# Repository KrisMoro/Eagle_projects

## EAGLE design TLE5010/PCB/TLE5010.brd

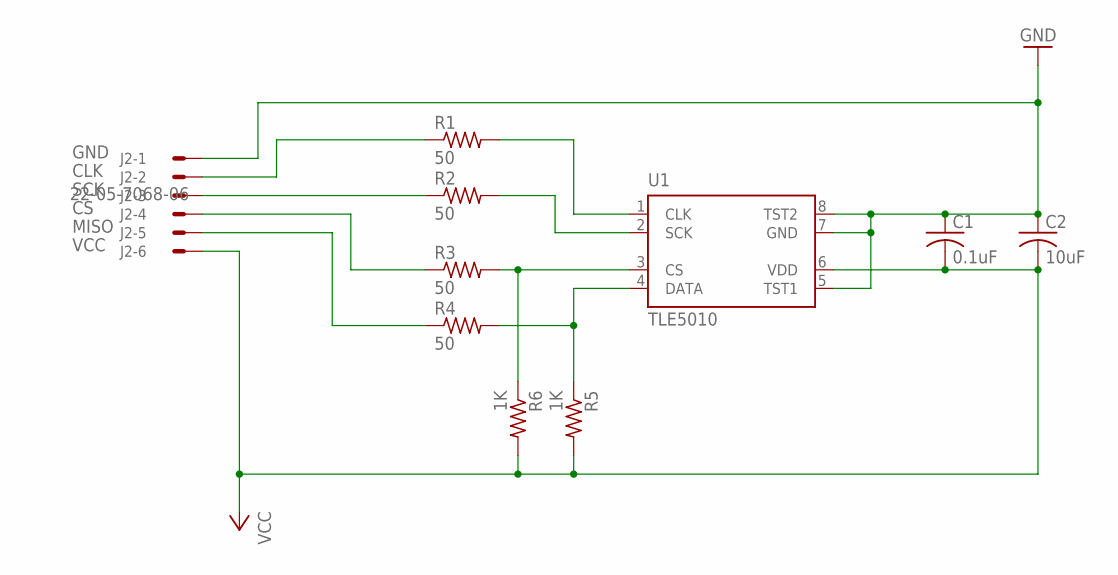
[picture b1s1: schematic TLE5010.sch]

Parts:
C1: 0.1uF; C1206
C2: 10uF; C1206
J2: 22-05-7068-06; 7395-06
R1, R2, R3, R4: 50; R1206
R5, R6: 1K; R1206
U1: TLE5010; PG-DSO-8

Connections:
CLK: J2.2, R1.1
CS: J2.4, R3.1
DATA: R4.2, R5.1, U1.4 (DATA)
GND: C1.1, C2.1, J2.1, U1.5 (TST1), U1.7 (GND), U1.8 (TST2)
MISO: J2.5, R4.1
unnamed: R1.2, U1.1 (CLK)
unnamed: R2.2, U1.2 (SCK)
unnamed: R3.2, R6.1, U1.3 (CS)
SCK: J2.3, R2.1
VCC: C1.2, C2.2, J2.6, R5.2, R6.2, U1.6 (VDD)

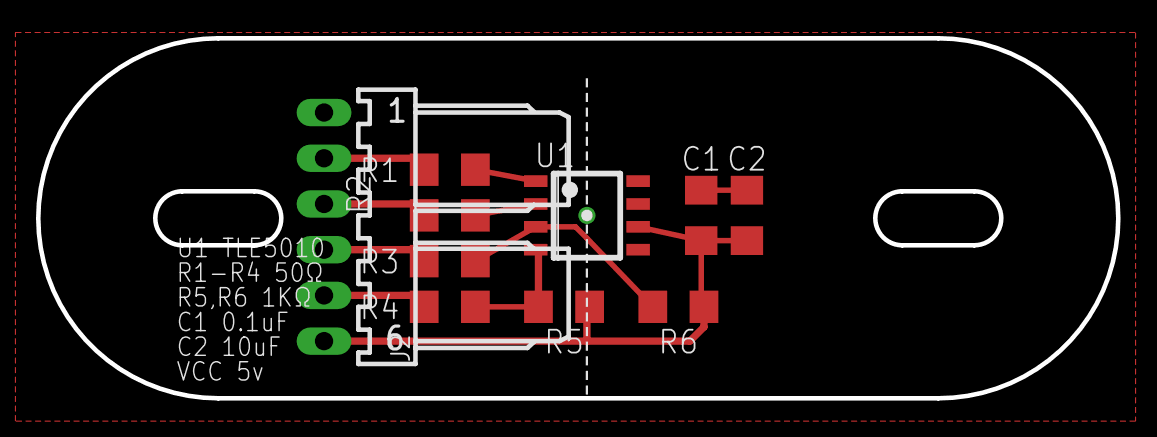
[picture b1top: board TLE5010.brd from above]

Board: 2 copper layers, 60.0 x 20.0 mm, 10 parts (0 on the bottom side), 10 nets.

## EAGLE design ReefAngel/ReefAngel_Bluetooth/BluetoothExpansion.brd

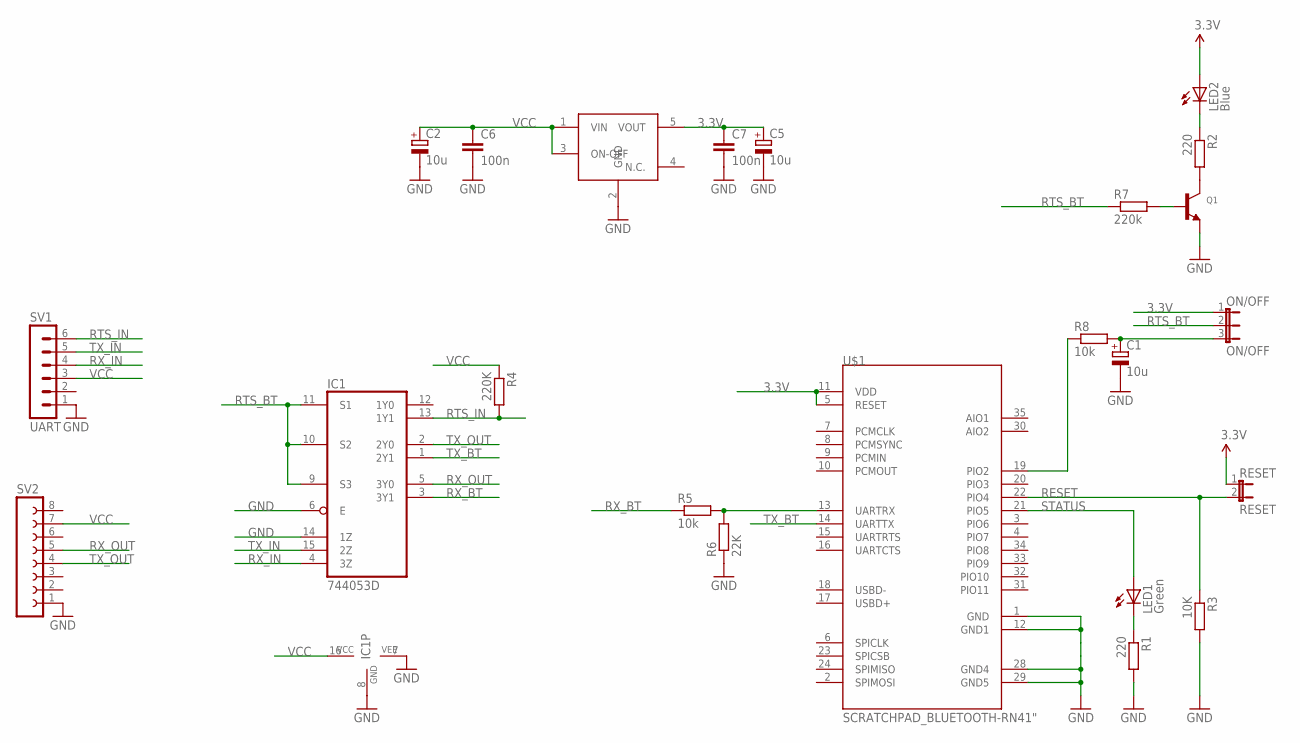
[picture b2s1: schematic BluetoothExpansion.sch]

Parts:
C1, C2, C5: 10u; A/3216-18W
C6, C7: 100n; C0805
IC1: 744053D; SO16
LED1: Green; LED3MM
LED2: Blue; LED3MM
ON/OFF: ON/OFF; JP2
Q1: TRANSISTOR_NPN; SOT23-R
R1, R2: 220; R0805
R3: 10K; R0805
R4: 220K; R0805
R5, R8: 10k; R0805
R6: 22K; R0805
R7: 220k; R0805
RESET: RESET; JP1
SV1: UART; MA06-1
SV2: FE08-1; FE08
U2: LP2985; SOT23-5
U$1: SCRATCHPAD_BLUETOOTH-RN41"; SCRATCHPAD_RN41

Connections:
3.3V: C5.+, C7.1, ON/OFF.1, U2.5 (VOUT), U$1.5 (RESET), U$1.11 (VDD)
GND: C1.-, C2.-, C5.-, C6.2, C7.2, IC1.6 (E), IC1.7 (VEE), IC1.8 (GND), IC1.14 (1Z), Q1.2 (E), R1.2, R3.2, R6.1, SV1.1, SV2.1, U2.2 (GND), U$1.1 (GND), U$1.12 (GND1), U$1.28 (GND4), U$1.29 (GND5)
unnamed: R5.2, R6.2, U$1.13 (UARTRX)
unnamed: R8.1, U$1.19 (PIO2)
unnamed: LED1.K (C), R1.1
unnamed: LED2.K (C), R2.1
unnamed: Q1.3 (C), R2.2
unnamed: C1.+, ON/OFF.3, R8.2
unnamed: Q1.1 (B), R7.2
RESET: R3.1, RESET.2, U$1.22 (PIO4)
RTS_BT: IC1.9 (S3), IC1.10 (S2), IC1.11 (S1), ON/OFF.2, R7.1
RTS_IN: IC1.13 (1Y1), R4.2, SV1.6
RX_BT: IC1.3 (3Y1), R5.1
RX_IN: IC1.4 (3Z), SV1.4
RX_OUT: IC1.5 (3Y0), SV2.5
STATUS: LED1.A, U$1.21 (PIO5)
TX_BT: IC1.1 (2Y1), U$1.14 (UARTTX)
TX_IN: IC1.15 (2Z), SV1.5
TX_OUT: IC1.2 (2Y0), SV2.4
VCC: C2.+, C6.1, IC1.16 (VCC), LED2.A, R4.1, RESET.1, SV1.3, SV2.7, U2.1 (VIN), U2.3 (ON-OFF)

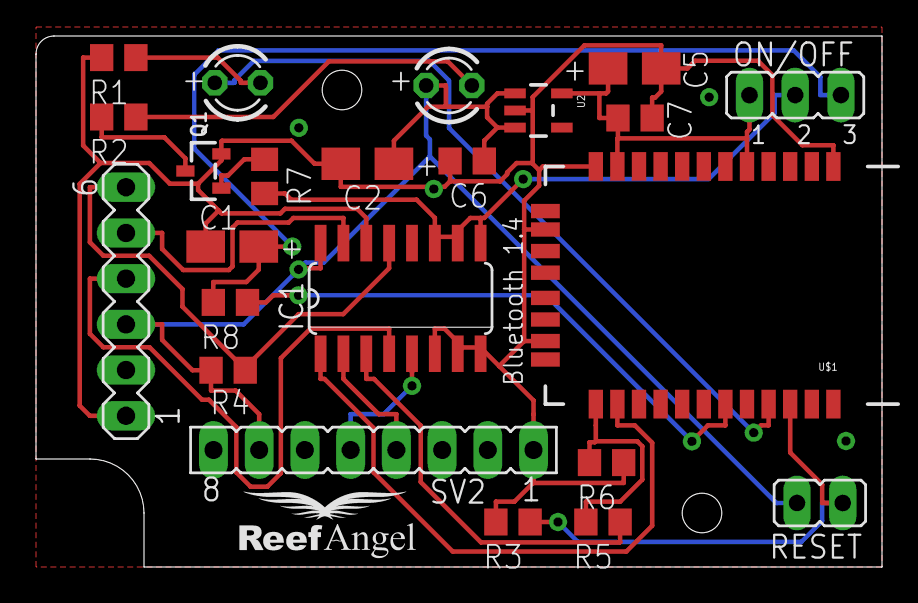
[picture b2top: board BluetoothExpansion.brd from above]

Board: 2 copper layers, 47.0 x 29.5 mm, 23 parts (0 on the bottom side), 20 nets.

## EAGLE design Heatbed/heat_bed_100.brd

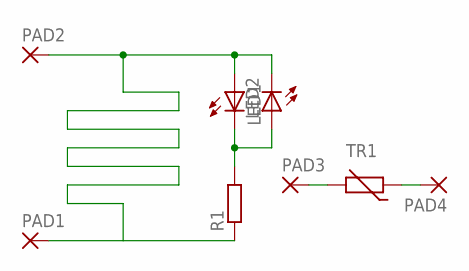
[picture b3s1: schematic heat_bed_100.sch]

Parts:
LED1, LED2: LEDSML0805; SML0805
PAD1, PAD2, PAD3, PAD4: 2,54/1,0
R1: R-EU_M1206; M1206
TR1: THERMISTOR_R-5; R-5

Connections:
unnamed: LED1.A, LED2.C, PAD1.1, PAD2.1, R1.1
unnamed: PAD3.1, TR1.2
unnamed: PAD4.1, TR1.1
unnamed: LED1.C, LED2.A, R1.2

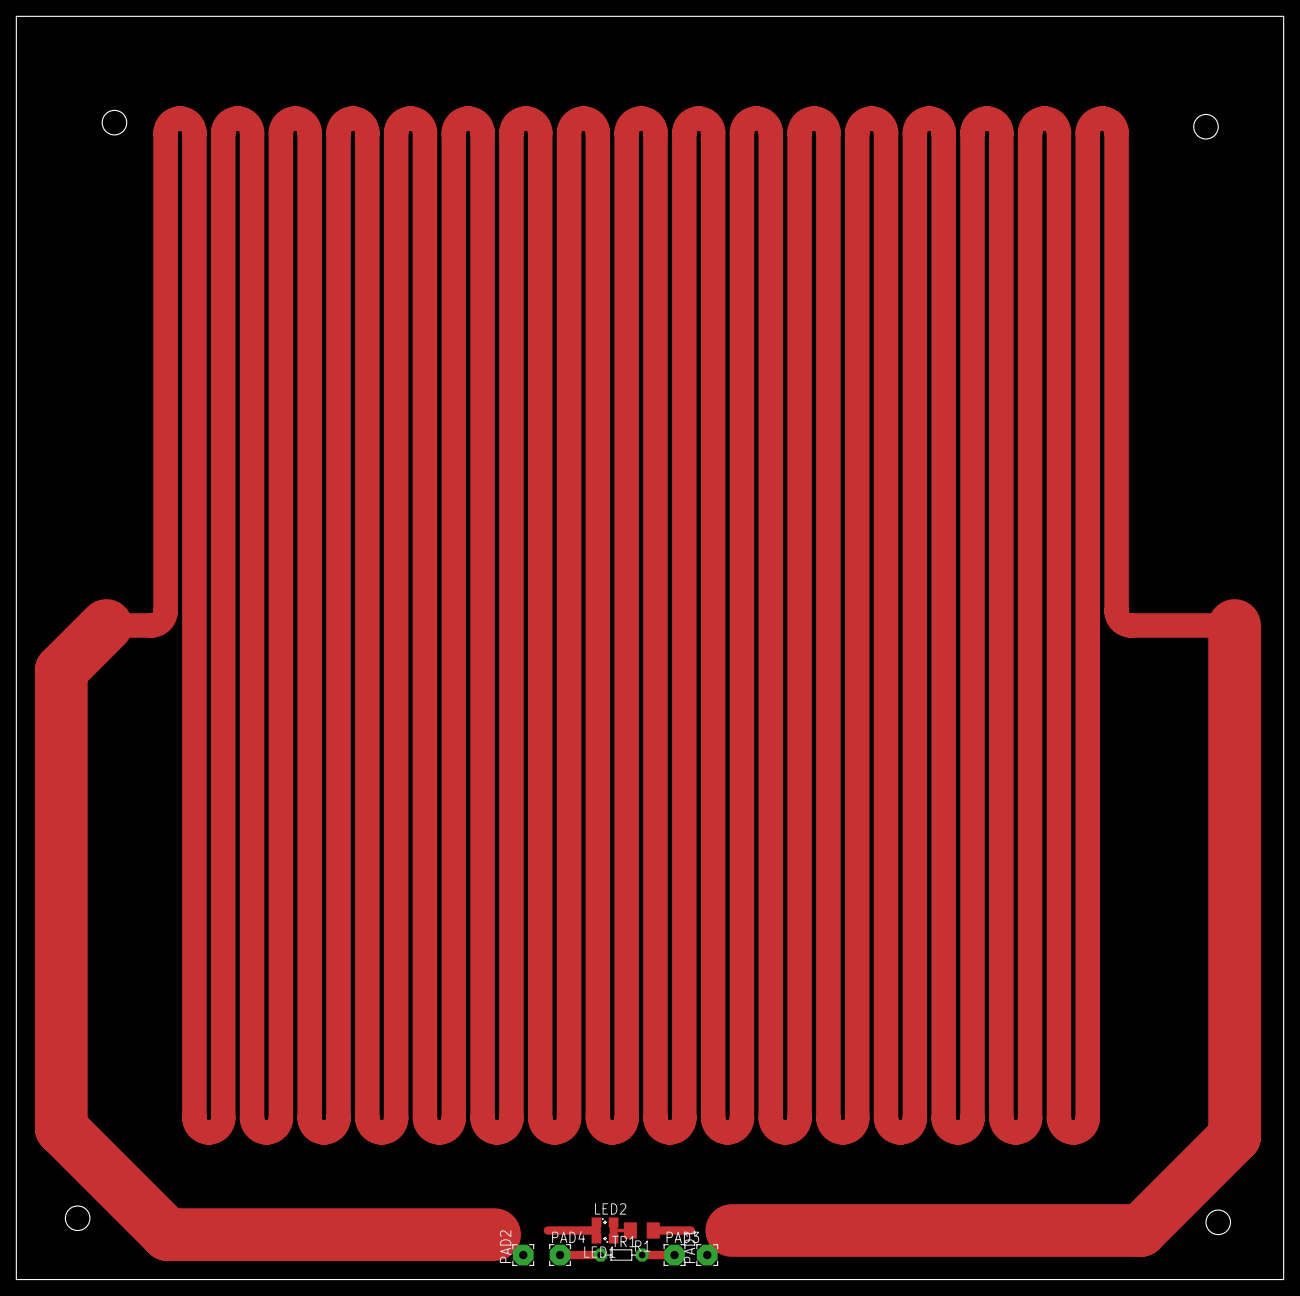
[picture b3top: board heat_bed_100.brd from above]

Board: 2 copper layers, 155.0 x 154.5 mm, 8 parts (0 on the bottom side), 4 nets.

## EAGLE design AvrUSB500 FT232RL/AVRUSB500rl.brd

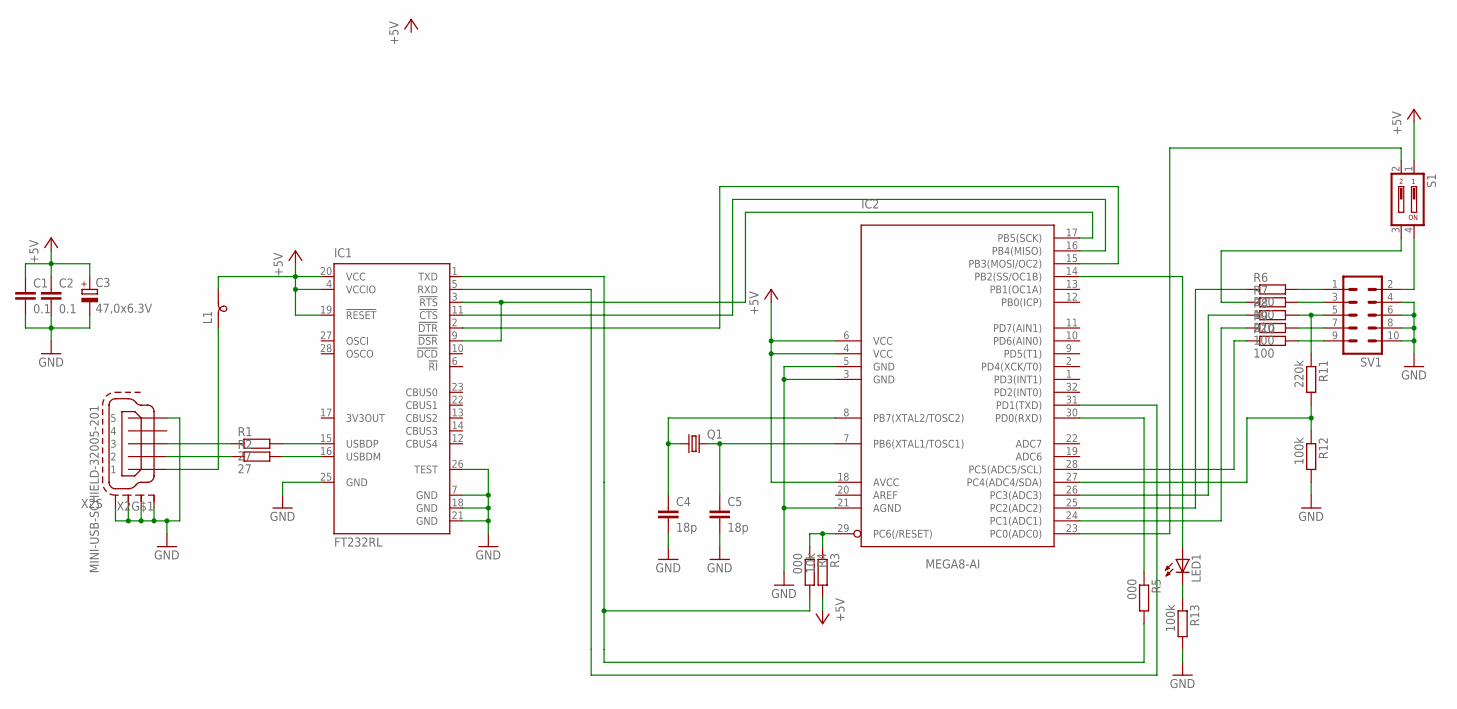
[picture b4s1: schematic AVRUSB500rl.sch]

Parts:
C1, C2: 0.1; C0805
C3: 47,0x6.3V; 153CLV-0605
C4, C5: 18p; C0805
IC1: FT232RL; SSOP28
IC2: MEGA8-AI; TQFP32-08
L1: SM-B5
LED1: LED3MM
Q1: CRYSTALHC49UP; HC49UP
R1, R2: 27; R0805
R3: 10k; R0805
R4, R5: 000; R0805
R6, R8: 220; R0805
R7, R9, R10: 100; R0805
R11: 220k; R0805
R12, R13: 100k; R0805
S1: DA02; DA-02
SV1: ML10L
X2: MINI-USB-SCHIELD-32005-201; 32005-201

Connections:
+5V: C1.1, C2.1, C3.+, IC2.4 (VCC), IC2.6 (VCC), IC2.18 (AVCC), R3.2, S1.1
GND: C1.2, C2.2, C3.-, C4.2, C5.2, IC1.7 (GND), IC1.18 (GND), IC1.21 (GND), IC1.25 (GND), IC1.26 (TEST), IC2.3 (GND), IC2.5 (GND), IC2.21 (AGND), R12.2, R13.2, SV1.4, SV1.6, SV1.8, SV1.10, X2.5, X2.M1 (S1), X2.M2 (S2), X2.M3 (S3), X2.M4 (S4)
unnamed: R1.1, X2.3
unnamed: IC1.15 (USBDP), R1.2
unnamed: R2.1, X2.2
unnamed: IC1.16 (USBDM), R2.2
unnamed: R6.2, SV1.1
unnamed: C4.1, IC2.8 (PB7(XTAL2/TOSC2)), Q1.1
unnamed: C5.1, IC2.7 (PB6(XTAL1/TOSC1)), Q1.2
unnamed: IC2.29 (PC6(/RESET)), R3.1, R4.1
unnamed: IC1.1 (TXD), R4.2, R5.2
unnamed: IC2.30 (PD0(RXD)), R5.1
unnamed: R7.2, SV1.3
unnamed: IC1.5 (RXD), IC2.31 (PD1(TXD))
unnamed: IC1.3 (!RTS), IC1.9 (!DSR), IC2.17 (PB5(SCK))
unnamed: IC1.11 (!CTS), IC2.16 (PB4(MISO))
unnamed: IC1.2 (!DTR), IC2.15 (PB3(MOSI/OC2))
unnamed: R8.2, R11.1, SV1.5
unnamed: R9.2, SV1.7
unnamed: R10.2, SV1.9
unnamed: IC2.27 (PC4(ADC4/SDA)), R11.2, R12.1
unnamed: IC2.28 (PC5(ADC5/SCL)), R10.1
unnamed: R7.1, S1.3
unnamed: L1.1, X2.1
unnamed: IC2.24 (PC1(ADC1)), R9.1
unnamed: IC2.26 (PC3(ADC3)), R8.1
unnamed: IC2.25 (PC2(ADC2)), R6.1
unnamed: S1.4, SV1.2
unnamed: IC2.23 (PC0(ADC0)), S1.2
unnamed: IC2.14 (PB2(SS/OC1B)), LED1.A
unnamed: LED1.K (C), R13.1
VCC: IC1.4 (VCCIO), IC1.19 (!RESET), IC1.20 (VCC), L1.2

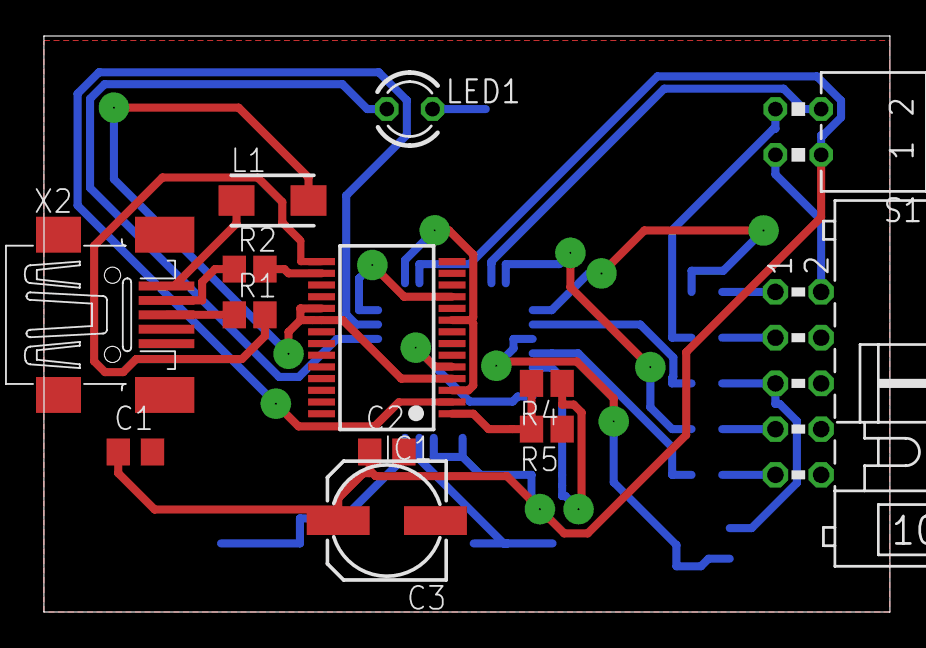
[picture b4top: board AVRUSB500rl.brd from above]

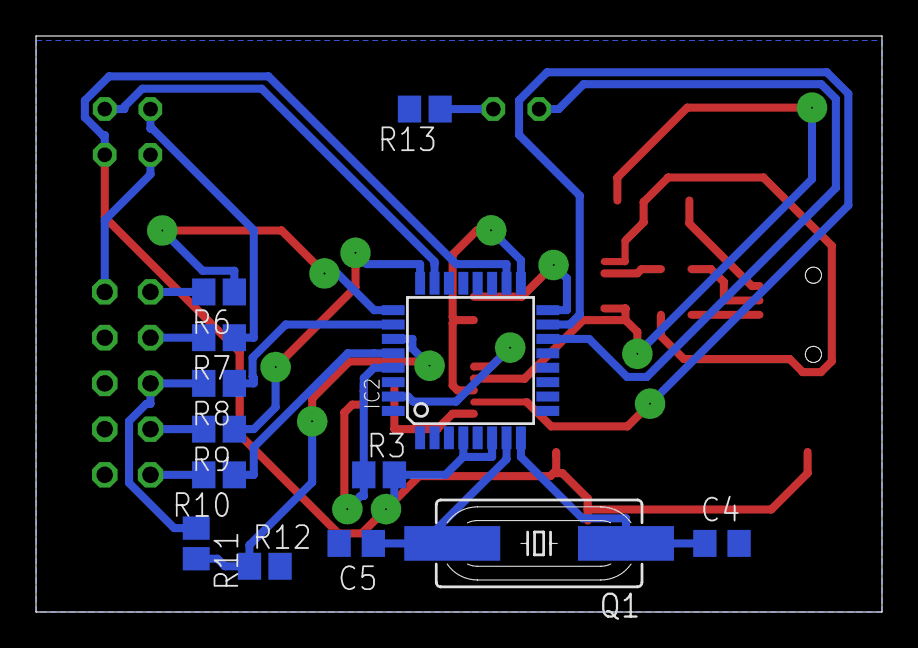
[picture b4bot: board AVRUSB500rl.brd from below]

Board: 2 copper layers, 47.0 x 32.0 mm, 26 parts (13 on the bottom side), 32 nets.

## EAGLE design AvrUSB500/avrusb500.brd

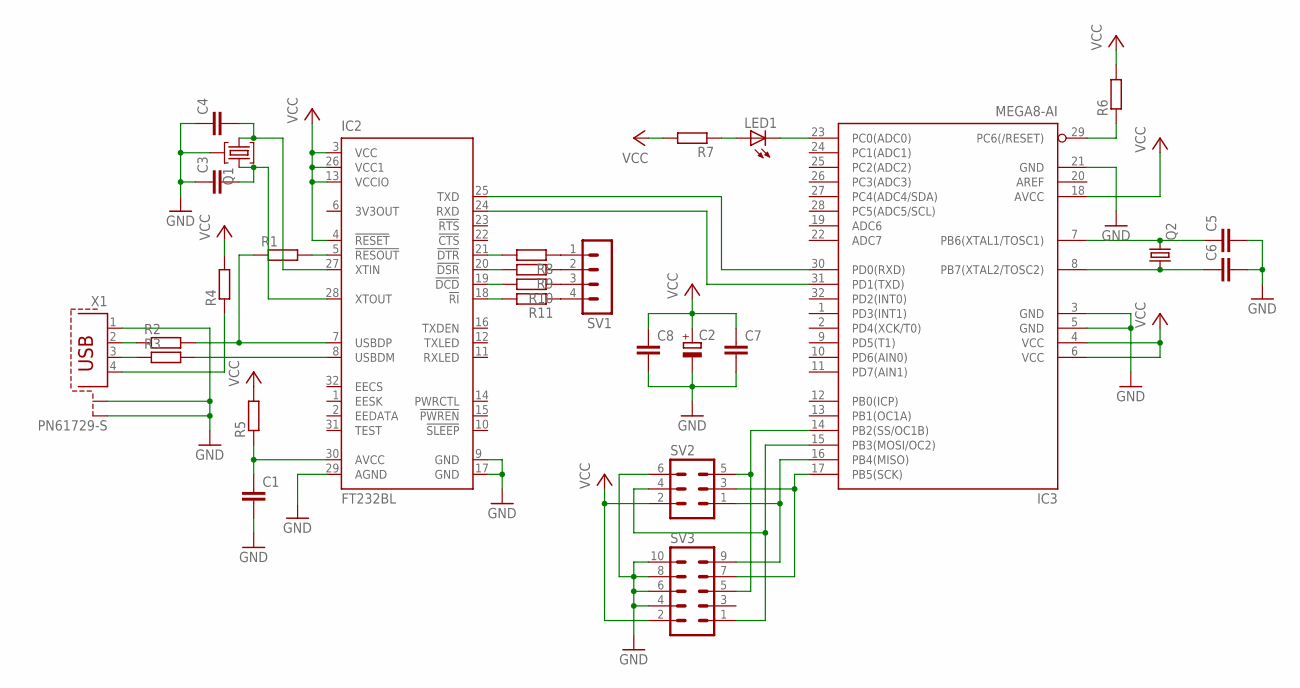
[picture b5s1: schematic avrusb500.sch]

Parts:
C1, C3, C4, C5, C6, C7, C8: C-EUC0805; C0805
C2: CPOL-EUSMCB; SMC_B
IC2: FT232BL; LQFP32-7X7
IC3: MEGA8-AI; TQFP32-08
LED1: LED5MM
Q1: HC49TL-H
Q2: CRYSTALHC49UP; HC49UP
R1, R2, R3, R4, R5, R6, R7, R8, R9, R10, R11: R-EU_R0805; R0805
SV1: MA04-1
SV2: ML6L
SV3: ML10L
X1: PN61729-S

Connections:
GND: C1.2, C2.-, C3.1, C4.1, C5.2, C6.2, C7.2, C8.2, IC2.9 (GND), IC2.17 (GND), IC2.29 (AGND), IC3.3 (GND), IC3.5 (GND), IC3.21 (GND), Q1.3, SV2.6, SV3.4, SV3.6, SV3.8, SV3.10, X1.1, X1.S1, X1.S2
unnamed: IC2.5 (!RESOUT), R1.2
unnamed: IC2.7 (USBDP), R1.1, R2.2
unnamed: IC2.8 (USBDM), R3.2
unnamed: R2.1, X1.2
unnamed: R3.1, X1.3
unnamed: R4.1, X1.4
unnamed: C1.1, IC2.30 (AVCC), R5.1
unnamed: C4.2, IC2.27 (XTIN), Q1.1
unnamed: C3.2, IC2.28 (XTOUT), Q1.2
unnamed: IC2.21 (!DTR), R8.2
unnamed: IC2.25 (TXD), IC3.30 (PD0(RXD))
unnamed: IC2.24 (RXD), IC3.31 (PD1(TXD))
unnamed: C5.1, IC3.7 (PB6(XTAL1/TOSC1)), Q2.2
unnamed: C6.1, IC3.8 (PB7(XTAL2/TOSC2)), Q2.1
unnamed: IC3.29 (PC6(/RESET)), R6.1
unnamed: IC3.15 (PB3(MOSI/OC2)), SV2.4, SV3.1
unnamed: IC3.16 (PB4(MISO)), SV2.1, SV3.9
unnamed: IC3.17 (PB5(SCK)), SV2.3, SV3.7
unnamed: IC3.14 (PB2(SS/OC1B)), SV2.5, SV3.5
unnamed: IC2.20 (!DSR), R9.2
unnamed: IC2.19 (!DCD), R10.2
unnamed: IC2.18 (!RI), R11.2
unnamed: R8.1, SV1.1
unnamed: LED1.A, R7.1
unnamed: IC3.23 (PC0(ADC0)), LED1.K (C)
unnamed: R9.1, SV1.2
unnamed: R10.1, SV1.3
unnamed: R11.1, SV1.4
VCC: C2.+, C7.1, C8.1, IC2.3 (VCC), IC2.4 (!RESET), IC2.13 (VCCIO), IC2.26 (VCC1), IC3.4 (VCC), IC3.6 (VCC), IC3.18 (AVCC), R4.2, R5.2, R6.2, R7.2, SV2.2, SV3.2

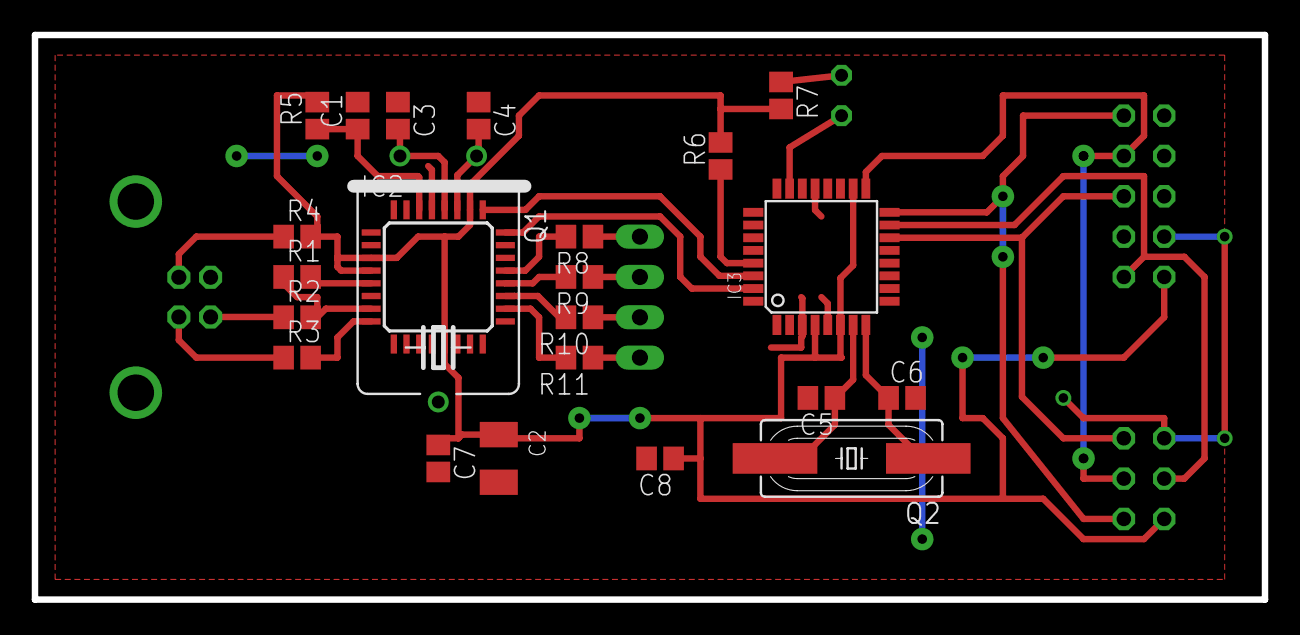
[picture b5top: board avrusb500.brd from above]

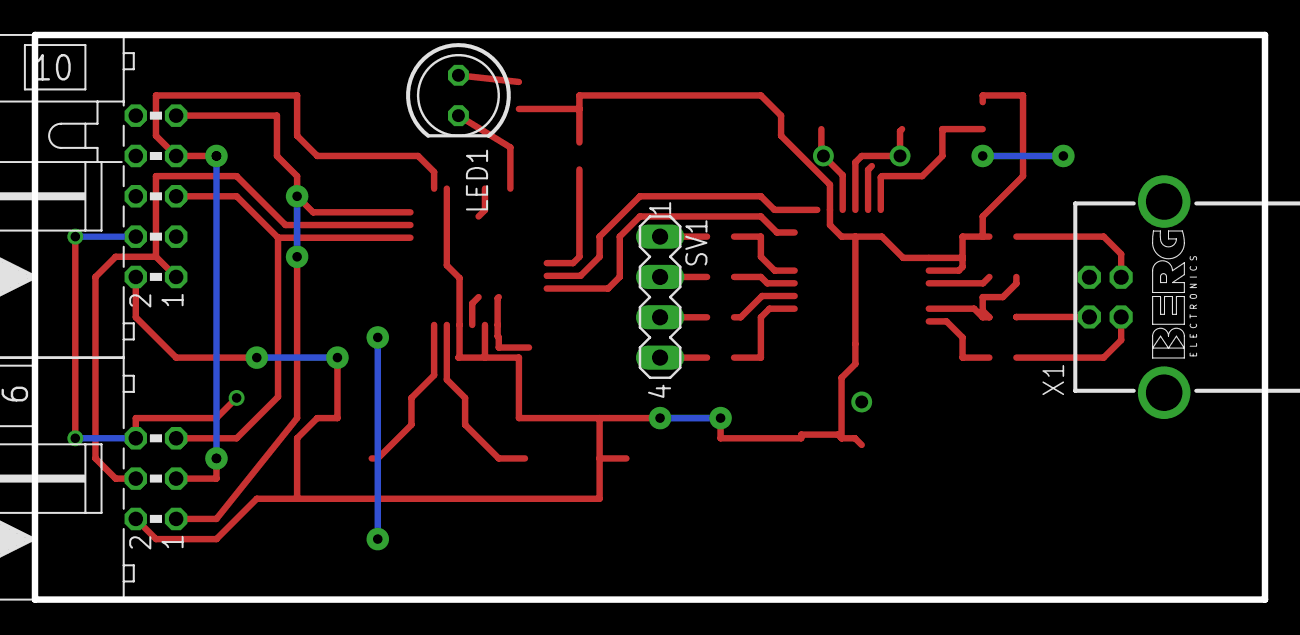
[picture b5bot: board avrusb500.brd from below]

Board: 2 copper layers, 77.5 x 35.6 mm, 28 parts (5 on the bottom side), 30 nets.

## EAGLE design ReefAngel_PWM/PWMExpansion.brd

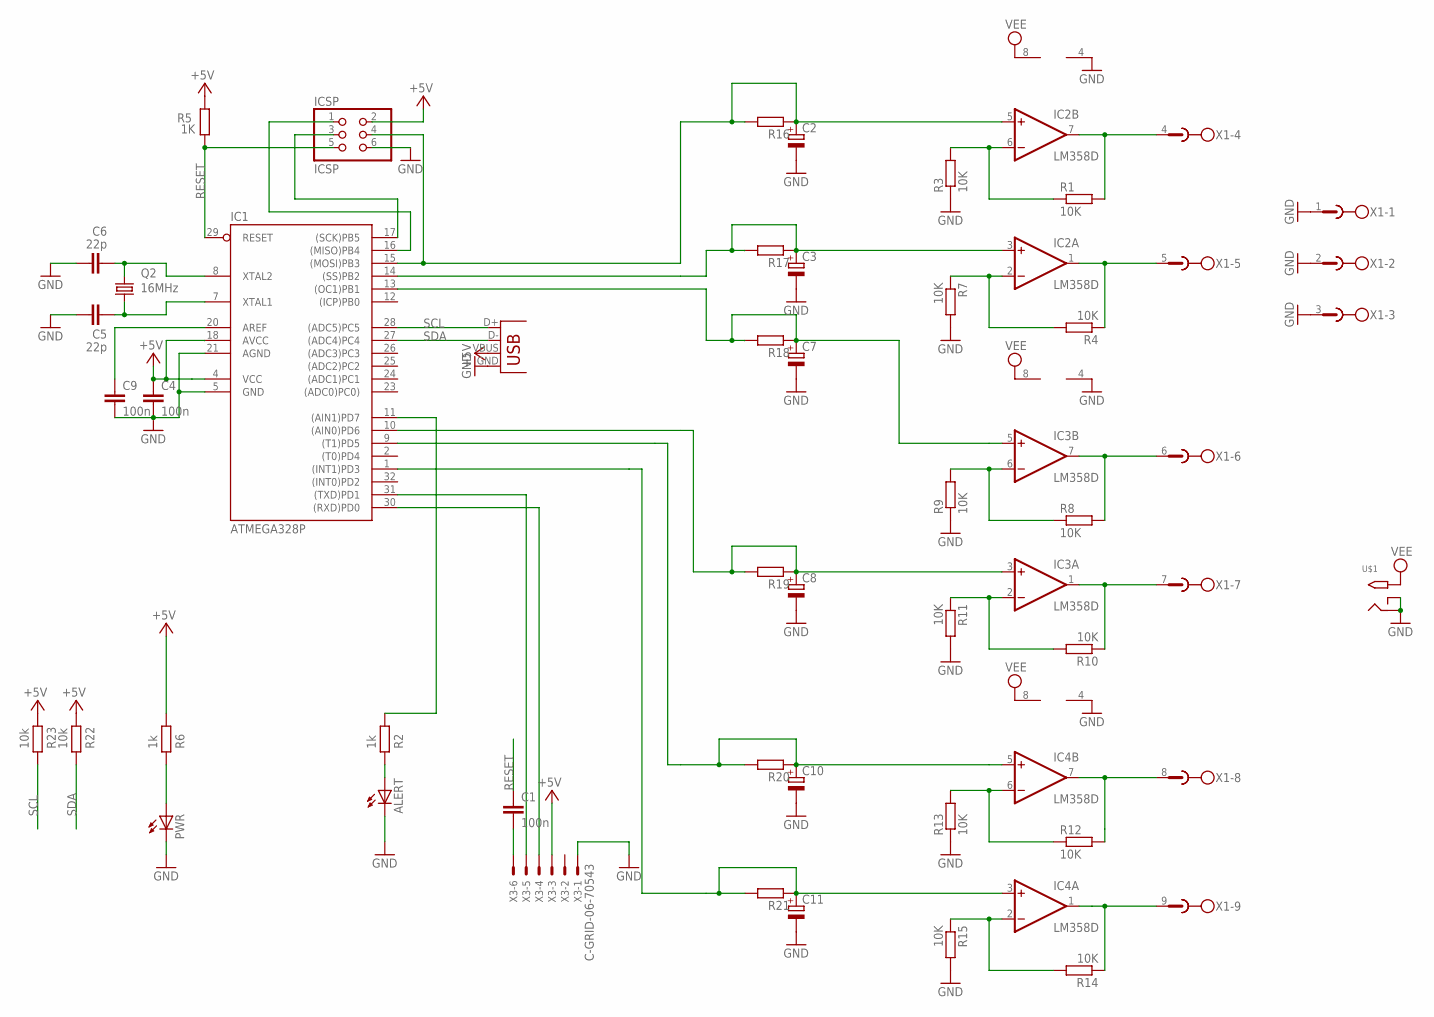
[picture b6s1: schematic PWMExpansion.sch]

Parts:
ALERT: LED3MM
C1, C4, C9: 100n; C0805
C2, C3, C7, C8, C10, C11: CPOL-EUA/3216-18W; A/3216-18W
C5, C6: 22p; C0805
IC1: ATMEGA328P; TQFP32-08
IC2, IC3, IC4: LM358D; SO08
ICSP: ICSP; 2X03
PWR: LED3MM
Q2: 16MHz; HC49/S
R1, R3, R4, R7, R8, R9, R10, R11, R12, R13, R14, R15: 10K; R0805
R2, R6: 1k; R0805
R5: 1K; R0805
R16, R17, R18, R19, R20, R21: R-EU_R0805; R0805
R22, R23: 10k; R0805
U$1: 2.1MMJACKTHM; PJ-102A
X1: MSTBV9
X3: C-GRID-06-70543; 70543-06
X5: USBSMD; USB-MINIB

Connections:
+5V: C4.1, IC1.4 (VCC), IC1.18 (AVCC), ICSP.2, R5.2, R6.1, R22.1, R23.1, X3.3, X5.VBUS
CTS: C1.2, X3.6
GND: ALERT.K (C), C2.-, C3.-, C4.2, C5.1, C6.1, C7.-, C8.-, C9.2, C10.-, C11.-, IC1.5 (GND), IC1.21 (AGND), IC2.4 (V-), IC3.4 (V-), IC4.4 (V-), ICSP.6, PWR.K (C), R3.1, R7.2, R9.1, R11.2, R13.1, R15.2, U$1.RING, U$1.RING_SW, X1.1, X1.2, X1.3, X3.1, X5.GND
MISO: IC1.16 ((MISO)PB4), ICSP.1
MOSI: C2.+, IC1.15 ((MOSI)PB3), IC2.5 (+IN), ICSP.4, R16.1, R16.2
MOSI1: C7.+, IC1.13 ((OC1)PB1), IC3.5 (+IN), R18.1, R18.2
MOSI2: C10.+, IC1.9 ((T1)PD5), IC4.5 (+IN), R20.1, R20.2
unnamed: C11.+, IC1.1 ((INT1)PD3), IC4.3 (+IN), R21.1, R21.2
unnamed: C8.+, IC1.10 ((AIN0)PD6), IC3.3 (+IN), R19.1, R19.2
unnamed: IC4.1 (OUT), R14.1, X1.9
unnamed: IC4.7 (OUT), R12.2, X1.8
unnamed: C3.+, IC1.14 ((SS)PB2), IC2.3 (+IN), R17.1, R17.2
unnamed: IC3.1 (OUT), R10.1, X1.7
unnamed: C5.2, IC1.7 (XTAL1), Q2.1
unnamed: IC3.6 (-IN), R8.1, R9.2
unnamed: C6.2, IC1.8 (XTAL2), Q2.2
unnamed: PWR.A, R6.2
unnamed: IC1.30 ((RXD)PD0), X3.4
unnamed: IC1.31 ((TXD)PD1), X3.5
unnamed: C9.1, IC1.20 (AREF)
unnamed: IC3.2 (-IN), R10.2, R11.1
unnamed: IC1.11 ((AIN1)PD7), R2.1
unnamed: IC3.7 (OUT), R8.2, X1.6
unnamed: IC4.6 (-IN), R12.1, R13.2
unnamed: IC4.2 (-IN), R14.2, R15.1
unnamed: IC2.1 (OUT), R4.1, X1.5
unnamed: IC2.7 (OUT), R1.2, X1.4
unnamed: IC2.6 (-IN), R1.1, R3.2
unnamed: IC2.2 (-IN), R4.2, R7.1
unnamed: ALERT.A, R2.2
RESET: C1.1, IC1.29 (RESET), ICSP.5, R5.1
SCK: IC1.17 ((SCK)PB5), ICSP.3
SCL: IC1.28 ((ADC5)PC5), R23.2, X5.D+
SDA: IC1.27 ((ADC4)PC4), R22.2, X5.D-
VEE: IC2.8 (V+), IC3.8 (V+), IC4.8 (V+), U$1.TIP

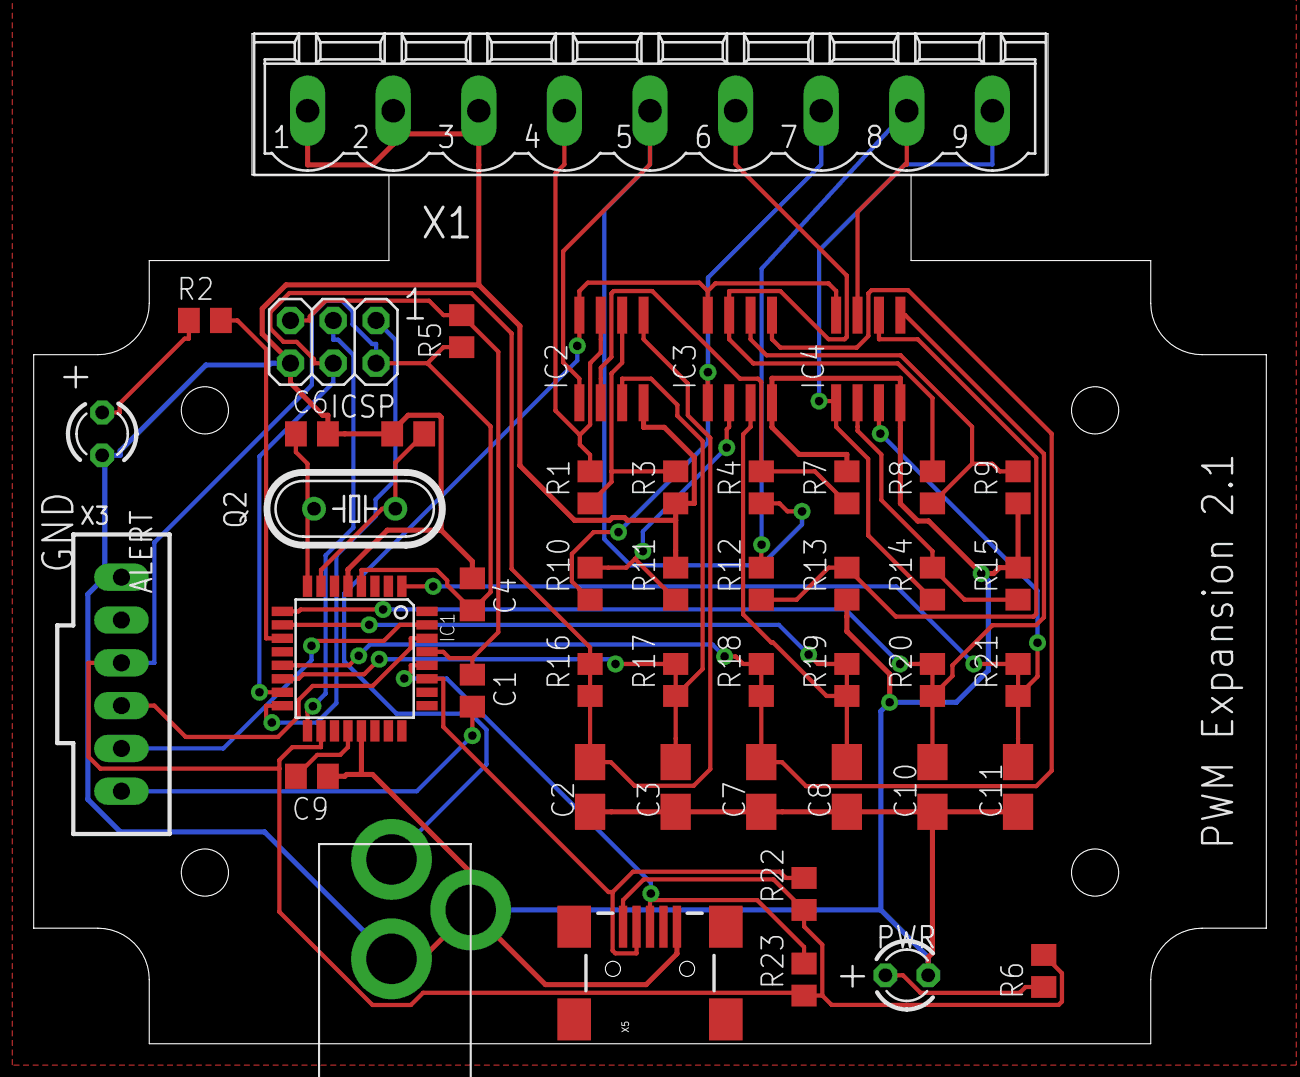
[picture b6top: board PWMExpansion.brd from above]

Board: 2 copper layers, 73.2 x 59.9 mm, 46 parts (0 on the bottom side), 35 nets.

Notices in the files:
parts and their libraries:
microbuilder: This work is placed in the public domain, and may be freely used for commercial and non-commercial work with the following conditions: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
